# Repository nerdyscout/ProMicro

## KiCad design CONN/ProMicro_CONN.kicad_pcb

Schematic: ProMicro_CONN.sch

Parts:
A1: Sparkfun_Pro_Micro
C2: 1µ; C_0603_1608Metric; MPN CL10A105KB8NNNC; LCSC# C15849
C3: 100n; C_0603_1608Metric; MPN CC0603KRX7R9BB104; LCSC# C14663
D1: LED; LED_0603_1608Metric; MPN 19-217/GHC-YR1S2/3T; LCSC# C72043
J1: AVR-JTAG-10; IDC-Header_2x05_P2.54mm_Vertical
J2: UEXT_Host; UEXT
J3: Display; PinHeader_1x04_P2.54mm_Vertical
LOGO1: Logo_Open_Hardware_Small; OSHW-Symbol_6.7x6mm_SilkScreen
R1, R2, R3, R4, R5, R6, R7, R9: 4k7; R_0603_1608Metric; MPN 0603WAF4701T5E; LCSC# C23162
R8: 1k; R_0603_1608Metric
SW1: reset; SW_SPST_B3U-1000P; MPN B3U-1000P
SW2: user; SW_SPST_B3U-1000P; MPN B3U-1000P

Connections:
+3V3: A1.21, C3.1, J1.4 (VREF), J1.7 (VCC), J2.1 (3V3), J3.2, R1.2, R2.2, R3.2, R4.2, R5.2, R6.2, R7.2
BTN: A1.9, SW2.2
CIPO: A1.15, J2.7 (MISO)
COPI: A1.14, J2.8 (MOSI)
CS1: A1.12, J2.10 (~SSEL)
GND: A1.3, A1.4, A1.23, C2.2, C3.2, D1.1 (K), J1.2 (GND), J1.10 (GND), J2.2 (GND), J3.1, R9.1, SW1.1
unnamed: D1.2 (A), R8.1
unnamed: R9.2, SW2.1
RXD: A1.1, J2.4 (RXD)
SCK: A1.16, J2.9 (SCK)
SCL: A1.6, J2.5 (SCL), J3.3, R3.1
SDA: A1.5, J2.6 (SDA), J3.4, R4.1
TCK: A1.20, J1.1 (TCK), R6.1, R8.2
TDI: A1.17, J1.9 (TDI), R1.1
TDO: A1.18, J1.3 (TDO), R2.1
TMS: A1.19, J1.5 (TMS), R5.1
TXD: A1.2, J2.3 (TXD)
~RST: A1.22, C2.1, J1.6 (~SRST), R7.1, SW1.2

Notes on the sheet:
Attention: RXD & TXD are swapped here!
uses internal pull-up

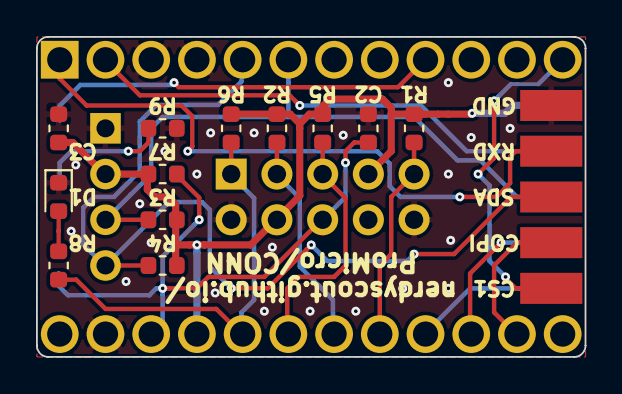
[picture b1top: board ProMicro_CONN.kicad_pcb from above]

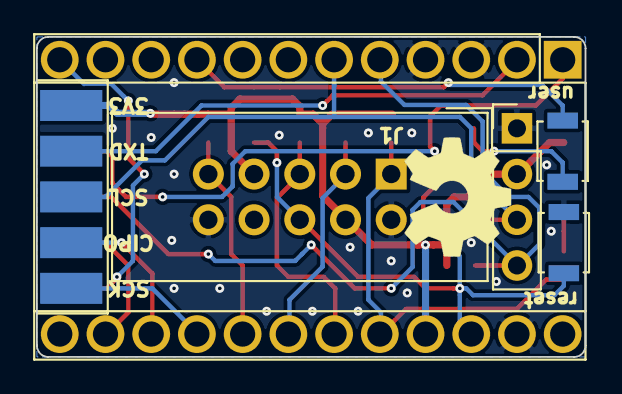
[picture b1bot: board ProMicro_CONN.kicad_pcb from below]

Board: 2 copper layers, 30.5 x 17.8 mm, 19 parts (7 on the bottom side), 18 nets.

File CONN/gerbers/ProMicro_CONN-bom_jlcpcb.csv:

Comment,Designator,Package,lcsc#,mpn
Sparkfun_Pro_Micro,A1,Sparkfun_Pro_Micro,,
100n,C3,C_0603_1608Metric,C14663,CC0603KRX7R9BB104
1µ,C2,C_0603_1608Metric,C15849,CL10A105KB8NNNC
LED,D1,LED_0603_1608Metric,C72043,19-217/GHC-YR1S2/3T
AVR-JTAG-10,J1,IDC-Header_2x05_P2.54mm_Vertical,,
Display,J3,PinHeader_1x04_P2.54mm_Vertical,,
UEXT_Host,J2,UEXT,,
Logo_Open_Hardware_Small,LOGO1,OSHW-Symbol_6.7x6mm_SilkScreen,,
1k,R8,R_0603_1608Metric,,
4k7,R1,R_0603_1608Metric,C23162,0603WAF4701T5E
4k7,R2,R_0603_1608Metric,C23162,0603WAF4701T5E
4k7,R3,R_0603_1608Metric,C23162,0603WAF4701T5E
4k7,R4,R_0603_1608Metric,C23162,0603WAF4701T5E
4k7,R5,R_0603_1608Metric,C23162,0603WAF4701T5E
4k7,R6,R_0603_1608Metric,C23162,0603WAF4701T5E
4k7,R7,R_0603_1608Metric,C23162,0603WAF4701T5E
4k7,R9,R_0603_1608Metric,C23162,0603WAF4701T5E
reset,SW1,SW_SPST_B3U-1000P,,B3U-1000P
user,SW2,SW_SPST_B3U-1000P,,B3U-1000P

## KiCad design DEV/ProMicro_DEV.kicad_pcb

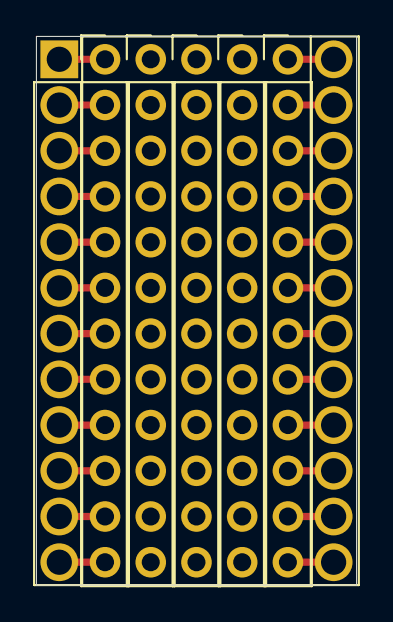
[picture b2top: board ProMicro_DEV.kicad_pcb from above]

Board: 2 copper layers, 17.8 x 30.5 mm, 6 parts (0 on the bottom side), 22 nets.

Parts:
A1: Sparkfun_Pro_Micro; ProMicro
J1, J2, J3, J4, J5: Conn_01x12; PinHeader_1x12_P2.54mm_Vertical

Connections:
+3V3: A1.21, J2.4
+5V: A1.24, J2.1
BTN: A1.9, J1.9
CIPO: A1.15, J2.10
COPI: A1.14, J2.11
CS0: A1.13, J2.12
CS1: A1.12, J1.12
D8: A1.11, J1.11
GND: A1.3, A1.4, A1.23, J1.3, J1.4, J2.2
INT: A1.10, J1.10
PWM: A1.8, J1.8
RXD: A1.1, J1.1
SCK: A1.16, J2.9
SCL: A1.6, J1.6
SDA: A1.5, J1.5
STAT: A1.7, J1.7
TCK: A1.20, J2.5
TDI: A1.17, J2.8
TDO: A1.18, J2.7
TMS: A1.19, J2.6
TXD: A1.2, J1.2
~RST: A1.22, J2.3

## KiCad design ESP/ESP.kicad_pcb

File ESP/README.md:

# ProMicro_ESP 
This module can be mounted to an [Arduino Pro Mini](https://www.sparkfun.com/products/11113), [Arduino Nano](https://store.arduino.cc/arduino-nano), [Sparkfun Pro Micro](https://www.sparkfun.com/products/12587), or any other pincompatible MCU running with 3.3V.

## Documentation 
All files can be found on [Github](https://github.com/nerdyscout/ProMicro/tree/master/ESP).

### Schematic

### BoM
  * [interactiveHTMLBoM](https://nerdyscout.github.io/ProMicro/ESP/docs/bom/ESP-ibom.html)
  * [octopart](docs/bom/ESP-bom_octopart.csv)

## Hardware 
### Layout

### Gerbers
can be found within the Github [repository](gerbers).

## Code  (unless otherwise stated)
 * [blink](examples/blink/blink.ino)

## external
### Links
  * [hackaday.io](https://hackaday.io/project/171898-promicro)

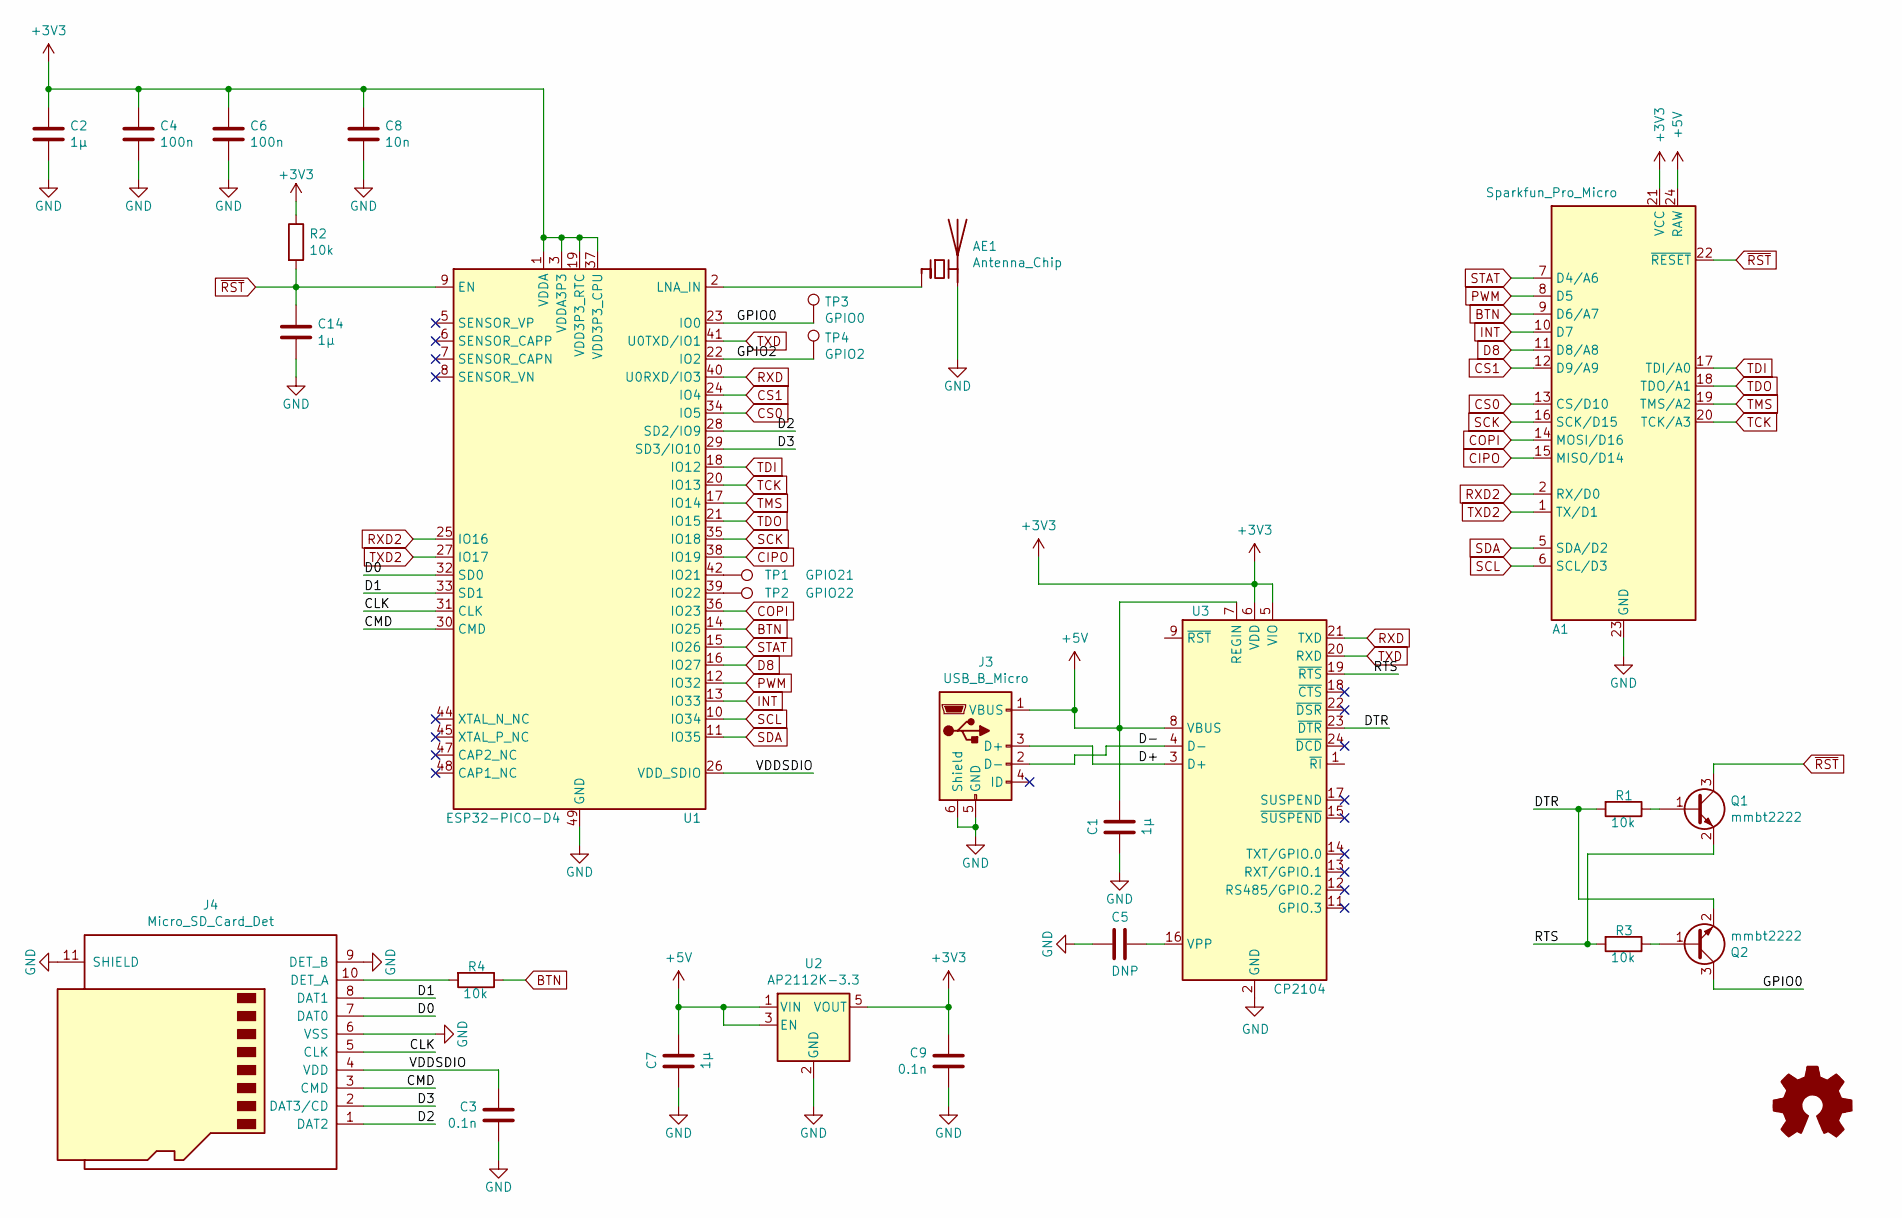
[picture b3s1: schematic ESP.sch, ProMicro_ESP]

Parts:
A1: Sparkfun_Pro_Micro; ProMicro
AE1: Antenna_Chip; SMD_ANT9520
C1, C2, C7, C14: 1µ; C_0603_1608Metric
C3, C9: 0.1n; C_0603_1608Metric
C4, C6: 100n; C_0603_1608Metric
C5: DNP; C_0603_1608Metric
C8: 10n; C_0603_1608Metric
J3: USB_B_Micro; USB_Micro-B_Molex_47346-0001
J4: Micro_SD_Card_Det; microSD_HC_Molex_104031-0811
LOGO1: Logo_Open_Hardware_Small; OSHW-Symbol_6.7x6mm_SilkScreen
Q1, Q2: mmbt2222; SOT-23
R1, R2, R3, R4: 10k; R_0603_1608Metric
TP1: GPIO21; PinHeader_1x01_P2.54mm_Vertical
TP2: GPIO22; PinHeader_1x01_P2.54mm_Vertical
TP3: GPIO0; PinHeader_1x01_P2.54mm_Vertical
TP4: GPIO2; PinHeader_1x01_P2.54mm_Vertical
U1: ESP32-PICO-D4; QFN-48-1EP_7x7mm_P0.5mm_EP5.3x5.3mm
U2: AP2112K-3.3; SOT-23-5
U3: CP2104; QFN-24-1EP_4x4mm_P0.5mm_EP2.6x2.6mm

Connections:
/CLK: J4.5 (CLK), U1.31 (CLK)
/CMD: J4.3 (CMD), U1.30 (CMD)
/D0: J4.7 (DAT0), U1.32 (SD0)
/D1: J4.8 (DAT1), U1.33 (SD1)
/D2: J4.1 (DAT2), U1.28 (SD2/IO9)
/D3: J4.2 (DAT3/CD), U1.29 (SD3/IO10)
/D+: J3.3 (D+), U3.3 (D+)
/D-: J3.2 (D-), U3.4 (D-)
/DTR: Q2.2 (E), R1.2, U3.23 (~DTR)
/GPIO0: Q2.3 (C), TP3.1, U1.23 (IO0)
/GPIO2: TP4.1, U1.22 (IO2)
/RTS: Q1.2 (E), R3.2, U3.19 (~RTS)
/VDDSDIO: C3.1, J4.4 (VDD), U1.26 (VDD_SDIO)
BTN: A1.9 (D6/A7), R4.1, U1.14 (IO25)
CIPO: A1.15 (MISO/D14), U1.38 (IO19)
COPI: A1.14 (MOSI/D16), U1.36 (IO23)
CS0: A1.13 (CS/D10), U1.34 (IO5)
CS1: A1.12 (D9/A9), U1.24 (IO4)
D8: A1.11 (D8/A8), U1.16 (IO27)
GND: A1.3 (GND), A1.4 (GND), A1.23 (GND), AE1.2 (PCB_Trace), C1.2, C2.2, C3.2, C4.2, C5.2, C6.2, C7.2, C8.2, C9.2, C14.2, J3.5 (GND), J3.6 (Shield), J4.6 (VSS), J4.9 (DET_B), J4.11 (SHIELD), U1.49 (GND), U2.2 (GND), U3.2 (GND), U3.25 (GND)
INT: A1.10 (D7), U1.13 (IO33)
unnamed: AE1.1 (FEED), U1.2 (LNA_IN)
unnamed: C5.1, U3.16 (VPP)
unnamed: J4.10 (DET_A), R4.2
unnamed: Q1.1 (B), R1.1
unnamed: Q2.1 (B), R3.1
unnamed: TP1.1, U1.42 (IO21)
unnamed: TP2.1, U1.39 (IO22)
PWM: A1.8 (D5), U1.12 (IO32)
RXD: U1.40 (U0RXD/IO3), U3.21 (TXD)
RXD2: A1.2 (RX/D0), U1.25 (IO16)
SCK: A1.16 (SCK/D15), U1.35 (IO18)
SCL: A1.6 (SCL/D3), U1.10 (IO34)
SDA: A1.5 (SDA/D2), U1.11 (IO35)
STAT: A1.7 (D4/A6), U1.15 (IO26)
TCK: A1.20 (TCK/A3), U1.20 (IO13)
TDI: A1.17 (TDI/A0), U1.18 (IO12)
TDO: A1.18 (TDO/A1), U1.21 (IO15)
TMS: A1.19 (TMS/A2), U1.17 (IO14)
TXD: U1.41 (U0TXD/IO1), U3.20 (RXD)
TXD2: A1.1 (TX/D1), U1.27 (IO17)
~RST: A1.22 (~RESET), C14.1, Q1.3 (C), R2.2, U1.9 (EN)

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
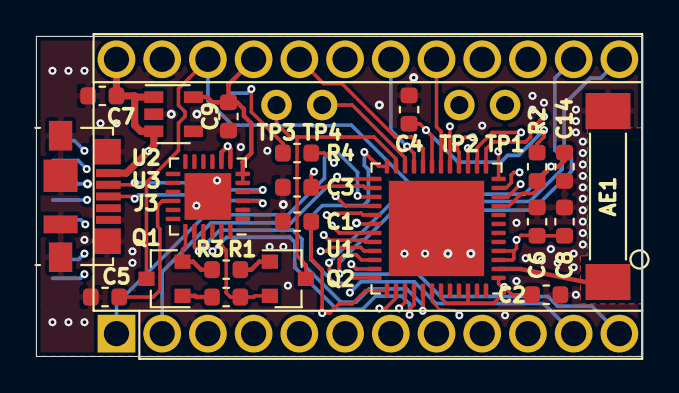
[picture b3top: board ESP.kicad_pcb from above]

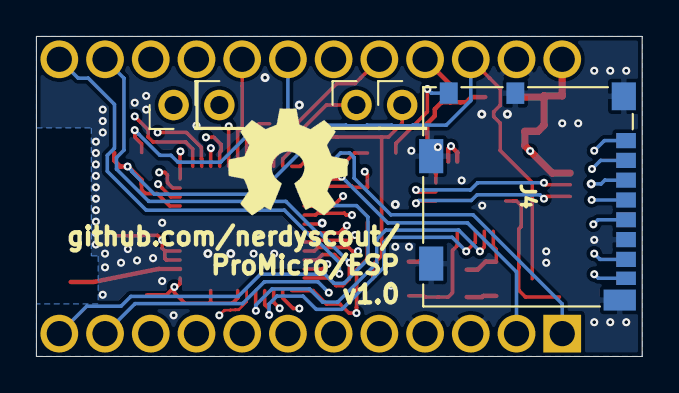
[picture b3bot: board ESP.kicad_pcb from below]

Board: 4 copper layers, 33.7 x 17.8 mm, 28 parts (6 on the bottom side), 44 nets.

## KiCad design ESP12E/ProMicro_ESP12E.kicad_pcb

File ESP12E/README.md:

# ProMicro_ESP12E
This module can be mounted to an [Arduino Pro Mini](https://www.sparkfun.com/products/11113), [Arduino Nano](https://store.arduino.cc/arduino-nano), [Sparkfun Pro Micro](https://www.sparkfun.com/products/12587), or any other pincompatible MCU running with 3.3V.

## Documentation
All files can be found on [Github](https://github.com/nerdyscout/ProMicro/tree/master/ESP12E).

### Schematic

### Layout

### BoM
  * [interactiveHTMLBoM](https://nerdyscout.github.io/ProMicro/ESP12E/docs/bom/ProMicro_ESP12E-ibom.html)
  * [octopart.csv](docs/bom/ProMicro_ESP12E-bom_octopart.csv)
  * [jlcpcb.csv](gerbers/ProMicro_ESP12E-bom_jlcpcb.csv)

## Gerbers
can be found within the Github [repository](gerbers).

## Links
  * [hackaday.io](https://hackaday.io/project/171898-promicro)

## License
Copyright Stefan Herold 2020

This documentation describes Open Hardware and is licensed under the CERN OHL v.1.2.

You may redistribute and modify this documentation under the terms of the CERN OHL v.1.2. (http://ohwr.org/cernohl). This documentation is distributed WITHOUT ANY EXPRESS OR IMPLIED WARRANTY, INCLUDING OF MERCHANTABILITY, SATISFACTORY QUALITY AND FITNESS FOR A PARTICULAR PURPOSE. Please see the CERN OHL v.1.2 for applicable conditions

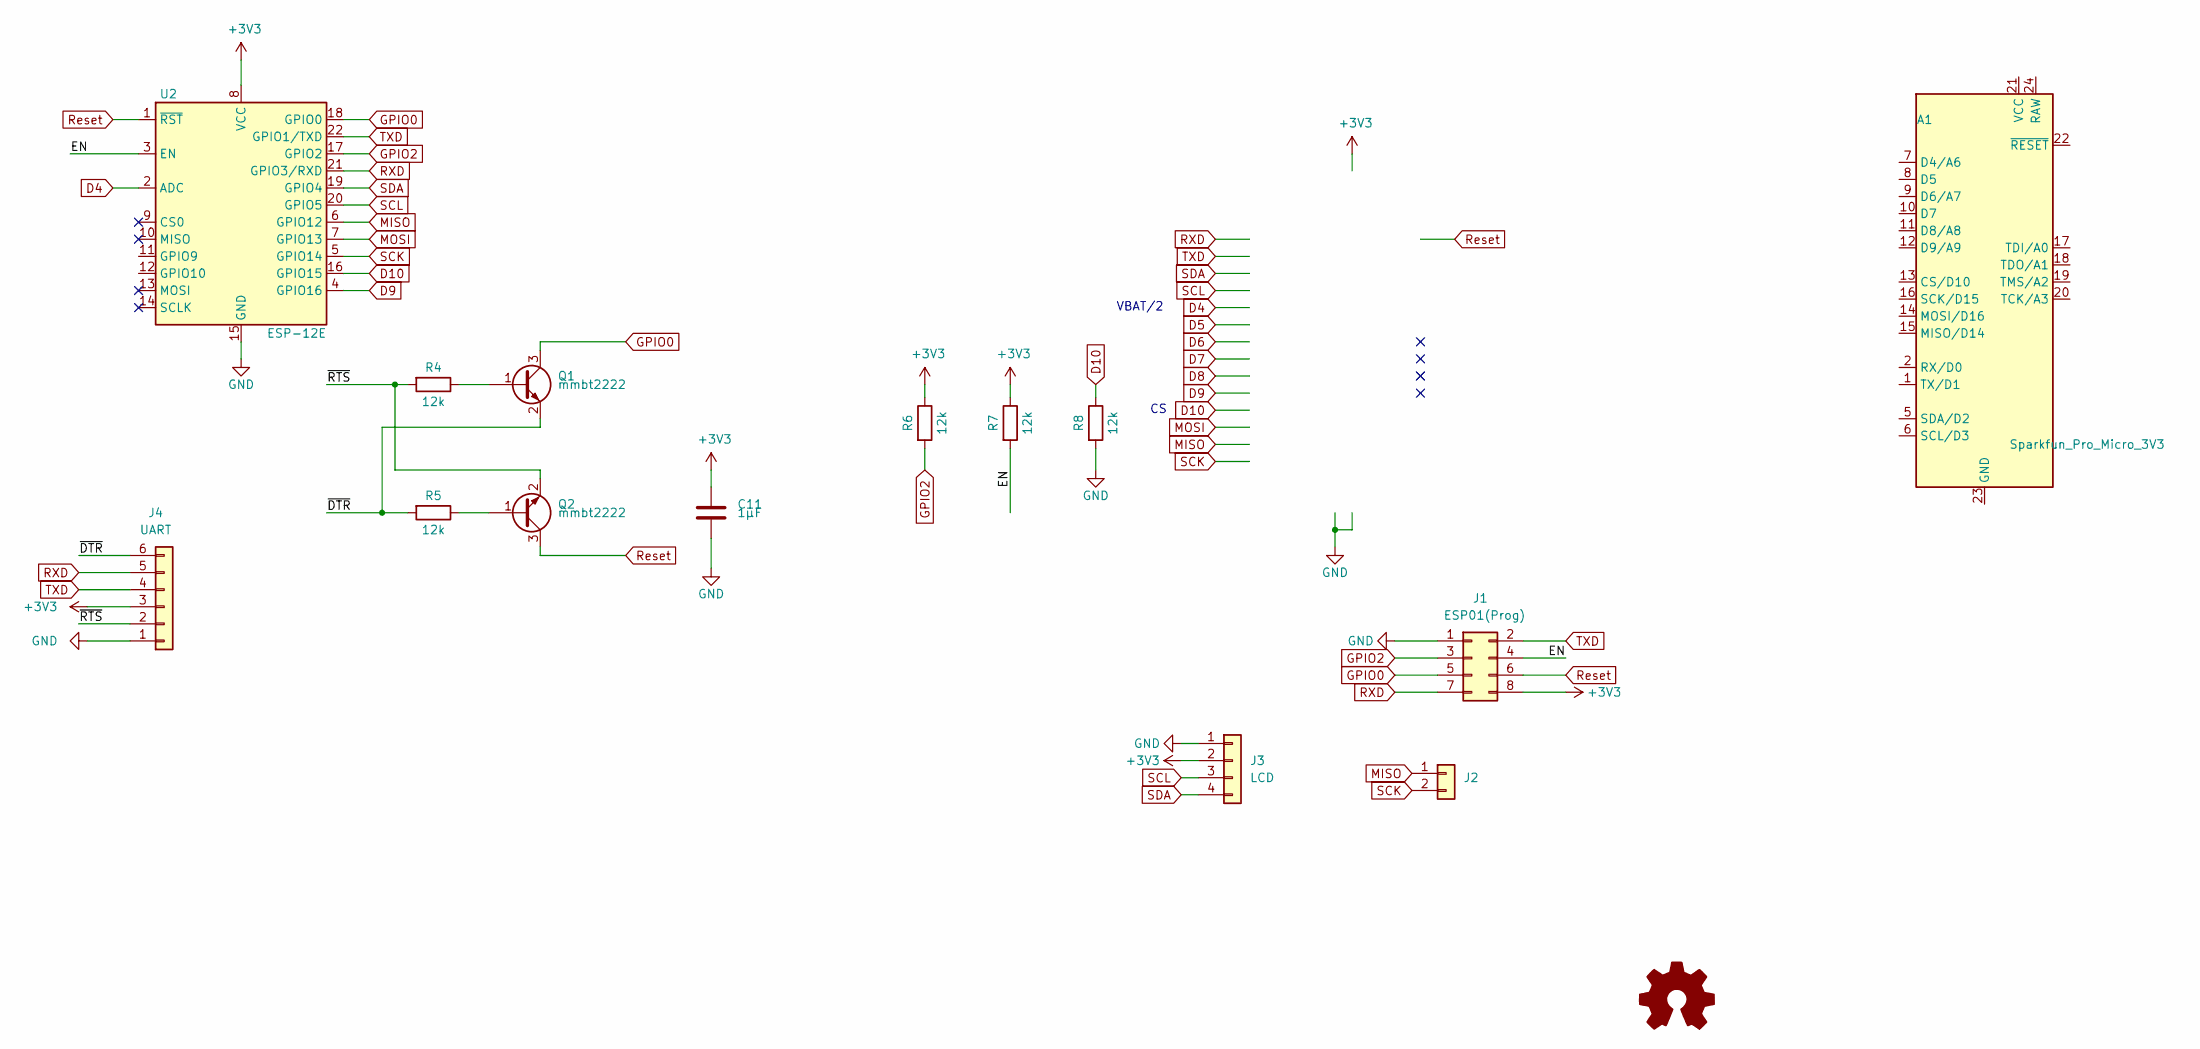
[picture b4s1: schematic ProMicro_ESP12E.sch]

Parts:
A1: Sparkfun_Pro_Micro_3V3; Sparkfun_Pro_Micro
C11: 1µF; C_0603_1608Metric
J1: ESP01(Prog); PinHeader_2x04_P2.54mm_Vertical
J2: Conn_01x02; PinHeader_1x02_P2.54mm_Vertical
J3: LCD; PinSocket_1x04_P2.54mm_Vertical
J4: UART; PinSocket_1x06_P2.54mm_Vertical
LOGO1: Logo_Open_Hardware_Small; OSHW-Symbol_6.7x6mm_SilkScreen
Q1, Q2: mmbt2222; SOT-23
R4, R5, R6, R7, R8: 12k; R_0603_1608Metric
U2: ESP-12E

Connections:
+3V3: A1.21 (VCC), C11.2, J1.8, J3.2, J4.3, R6.1, R7.1, U2.8 (VCC)
/EN: J1.4, R7.2, U2.3 (EN)
/~DTR: J4.6, Q1.2 (E), R5.2
/~RTS: J4.2, Q2.2 (E), R4.2
D4: A1.7 (D4/A6), U2.2 (ADC)
D9: A1.12 (D9/A9), U2.4 (GPIO16)
D10: A1.13 (CS/D10), R8.1, U2.16 (GPIO15)
GPIO0: J1.5, Q1.3 (C), U2.18 (GPIO0)
GPIO2: J1.3, R6.2, U2.17 (GPIO2)
MISO: A1.15 (MISO/D14), J2.1, U2.6 (GPIO12)
MOSI: A1.14 (MOSI/D16), U2.7 (GPIO13)
unnamed: Q1.1 (B), R4.1
unnamed: Q2.1 (B), R5.1
RXD: A1.2 (RX/D0), J1.7, J4.5, U2.21 (GPIO3/RXD)
Reset: A1.22 (~RESET), J1.6, Q2.3 (C), U2.1 (~RST)
SCK: A1.16 (SCK/D15), J2.2, U2.5 (GPIO14)
SCL: A1.6 (SCL/D3), J3.3, U2.20 (GPIO5)
SDA: A1.5 (SDA/D2), J3.4, U2.19 (GPIO4)
TXD: A1.1 (TX/D1), J1.2, J4.4, U2.22 (GPIO1/TXD)

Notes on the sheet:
VBAT/2

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
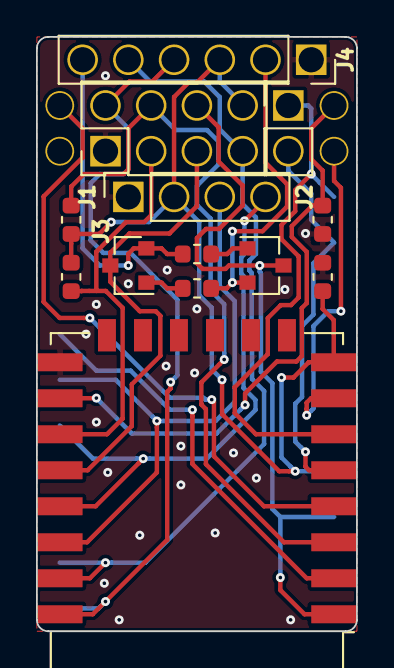
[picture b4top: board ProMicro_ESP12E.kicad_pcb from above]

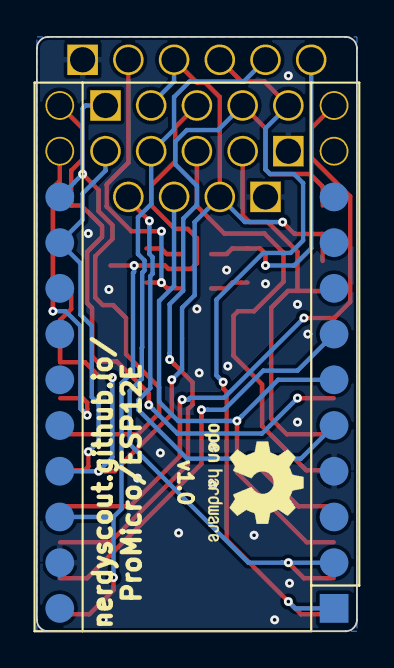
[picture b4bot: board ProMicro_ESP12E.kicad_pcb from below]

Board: 2 copper layers, 17.8 x 33.0 mm, 15 parts (2 on the bottom side), 20 nets.

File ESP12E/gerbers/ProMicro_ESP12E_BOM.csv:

Component;Description;Part;References;Value;Footprint;Quantity Per PCB;Datasheet
1;Unpolarized capacitor;C;C11;1µF;C_0603_1608Metric;1;~
2;Generic connector, single row, 01x02, script generated (kicad-library-utils/schlib/autogen/connector/);Conn_01x02;J2;Conn_01x02;PinHeader_1x02_P2.54mm_Vertical;1;~
3;Generic connector, double row, 02x04, odd/even pin numbering scheme (row 1 odd numbers, row 2 even numbers), script generated (kicad-library-utils/schlib/autogen/connector/);Conn_02x04_Odd_Even;J1;ESP01(Prog);PinHeader_2x04_P2.54mm_Vertical;1;~
4;Generic connector, single row, 01x04, script generated (kicad-library-utils/schlib/autogen/connector/);Conn_01x04;J3;LCD;PinSocket_1x04_P2.54mm_Vertical;1;~
5;Generic connector, single row, 01x06, script generated (kicad-library-utils/schlib/autogen/connector/);Conn_01x06;J4;UART;PinSocket_1x06_P2.54mm_Vertical;1;~
6;NPN transistor, base/emitter/collector;Q_NPN_BEC;Q1 Q2;mmbt2222;SOT-23;2;~
7;Resistor;R;R4 R5 R6 R7 R8;12k;R_0603_1608Metric;5;~
8;802.11 b/g/n Wi-Fi Module;ESP-12E;U2;ESP-12E;ESP-12E;1;http://wiki.ai-thinker.com/_media/esp8266/esp8266_series_mod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

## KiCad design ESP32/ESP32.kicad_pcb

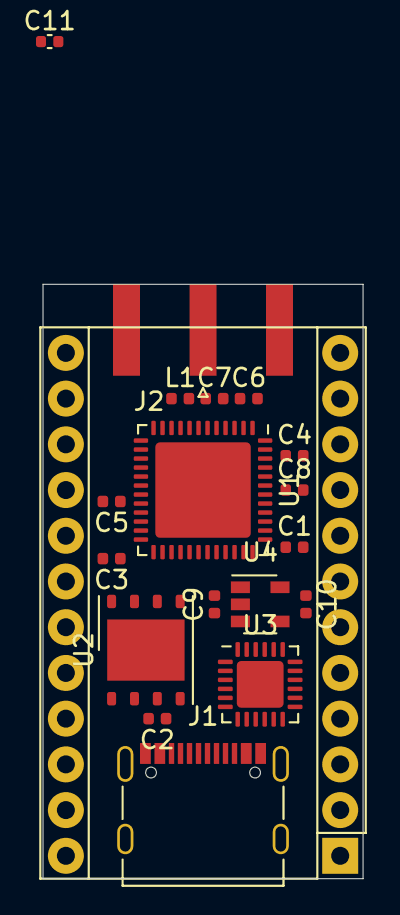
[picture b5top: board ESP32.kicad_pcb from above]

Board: 2 copper layers, 17.8 x 33.0 mm, 20 parts (1 on the bottom side), 24 nets, no tracks yet.

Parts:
A1: Sparkfun_Pro_Micro
C1, C2, C3, C4, C5, C8, C9, C10, C11: 100n; C_0402_1005Metric
C6: 0.75pF; C_0402_1005Metric
C7: 1.5pF; C_0402_1005Metric
J1: USB_C_Receptacle_USB2.0; USB_C_Receptacle_Palconn_UTC16-G
J2: Conn_Coaxial; SMA_Amphenol_132289_EdgeMount
L1: 7.5nH; L_0402_1005Metric
LOGO1: Logo_Open_Hardware_Small; OSHW-Symbol_6.7x6mm_SilkScreen
U1: ESP32-PICO-D4; QFN-48-1EP_7x7mm_P0.5mm_EP5.3x5.3mm
U2: W25Q32JVZP; WSON-8-1EP_6x5mm_P1.27mm_EP3.4x4.3mm
U3: CP2104; QFN-24-1EP_4x4mm_P0.5mm_EP2.6x2.6mm
U4: AP2112K-3.3; SOT-23-5

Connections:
+3V3: A1.21, C1.1, C4.1, C5.1, C8.1, C10.1, C11.1, U1.1, U1.3, U1.4, U1.19, U1.37, U1.43, U1.46, U4.5
/CMD: U1.30, U2.1
/D+: J1.A6, J1.B6, U3.3
/D-: J1.A7, J1.B7, U3.4
/DAT0: U1.32, U2.5
/DAT1: U1.33, U2.2
/DAT2: U1.28, U2.3
/DAT3: U1.29, U2.7
/SCLK: U1.31, U2.6
/VDD_SDIO: C3.1, U1.26, U2.8
GND: A1.3, A1.4, A1.23, C1.2, C2.2, C3.2, C4.2, C5.2, C6.2, C8.2, C9.2, C10.2, C11.2, J1.A1, J1.A12, J1.B1, J1.B12, J1.S1, J2.2, L1.1, U1.49, U2.4, U2.9, U3.2, U3.25, U4.2
unnamed: C6.1, C7.2, U1.2
unnamed: C7.1, J2.1, L1.2
unnamed: U3.5, U3.6
RXD: A1.1, U1.25
TCK: A1.20, U1.20
TDI: A1.17, U1.18
TDO: A1.18, U1.21
TMS: A1.19, U1.17
TXD: A1.2, U1.27
USB_RXD: U1.40, U3.21
USB_TXD: U1.41, U3.20
VBUS: C2.1, C9.1, J1.A4, J1.A9, J1.B4, J1.B9, U3.7, U3.8, U4.1, U4.3
~RST: A1.22, U1.9, U3.9

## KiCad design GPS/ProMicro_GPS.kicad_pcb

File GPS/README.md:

# ProMicro_GPS
This module can be mounted to an [Arduino Pro Mini](https://www.sparkfun.com/products/11113), [Arduino Nano](https://store.arduino.cc/arduino-nano), [Sparkfun Pro Micro](https://www.sparkfun.com/products/12587), or any other pincompatible MCU running with 3.3V. Depending on assembly it provides GPS and/or GYRO data. Manufacturing this PCB with 0.8mm thickness allows to mount a LORA module onto its back.

## Documentation
All files can be found on [Github](https://github.com/nerdyscout/ProMicro/tree/master/GPS).

### Schematic

### Layout

### BoM
  * [interactiveHTMLBoM](https://nerdyscout.github.io/ProMicro/GPS/docs/BOM/ProMicro_GPS.html)
  * [kicost](docs/BOM/ProMicro_GPS.xlsx)
  * [csv](docs/BOM/ProMicro_GPS.csv)

## Gerbers
can be found within the Github [repository](gerbers).

## Code
| | GYRO | GPS |
| --- | --- | --- |
| Arduino Nano | tbd | [GPS](examples/Arduino_Nano_GPS/Arduino_Nano_GPS.ino) |
| Sparkfun ProMicro | [ICM20948](examples/Sparkfun_ProMicro_ICM20948/Sparkfun_ProMicro_ICM20948.ino)<br>[MPU9250](examples/Sparkfun_ProMicro_MPU9250/Sparkfun_ProMicro_MPU9250.ino) | [GPS](examples/Sparkfun_ProMicro_GPS/Sparkfun_ProMicro_GPS.ino) |

## Links
  * [hackaday.io](https://hackaday.io/project/171898-promicro)

## License
Copyright Stefan Herold 2020

This documentation describes Open Hardware and is licensed under the CERN OHL v.1.2.

You may redistribute and modify this documentation under the terms of the CERN OHL v.1.2. (http://ohwr.org/cernohl). This documentation is distributed WITHOUT ANY EXPRESS OR IMPLIED WARRANTY, INCLUDING OF MERCHANTABILITY, SATISFACTORY QUALITY AND FITNESS FOR A PARTICULAR PURPOSE. Please see the CERN OHL v.1.2 for applicable conditions

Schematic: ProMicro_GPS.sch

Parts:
A1: Sparkfun_Pro_Micro_3V3; Sparkfun_Pro_Micro
C1: 100n; C_0402_1005Metric; LCSC# C15195
C2, C3, C4, C5, C7, C9: 100n; C_0402_1005Metric; LCSC# C1525
C6: 10n; C_0402_1005Metric; LCSC# C15195
C8: 4,7µ; C_0603_1608Metric; LCSC# C19666
C10, C11: DNP; C_0402_1005Metric
D1: LED; LED_0603_1608Metric; LCSC# C72041
H2: MountingHole; MountingHole_2.1mm
J1: uFL; U.FL_Hirose_U.FL-R-SMT-1_Vertical
J2: Coax; SMA_Samtec_SMA-J-P-H-ST-EM1_EdgeMount
JP1, JP4: SolderJumper_2_Open; SolderJumper-2_P1.3mm_Open_RoundedPad1.0x1.5mm
JP2: Jumper_NO_Small; SolderJumper-2_P1.3mm_Open_RoundedPad1.0x1.5mm
JP3: Jumper_NC_Small; SolderJumper-2_P1.3mm_Bridged_RoundedPad1.0x1.5mm
L1: 27n; L_0402_1005Metric
LOGO1: Logo_Open_Hardware_Small; OSHW-Symbol_6.7x6mm_SilkScreen
R1: 10; R_0402_1005Metric
R2: 0; R_0402_1005Metric; LCSC# C17168
R3: 1k; R_0402_1005Metric; LCSC# C11702
R4, R5: 4k7; R_0402_1005Metric; LCSC# C25900
TP1: AUX_SDA; TestPoint_Pad_D1.5mm
TP2: AUX_SCL; TestPoint_Pad_D1.5mm
TP3: FSYNC; TestPoint_Pad_D1.5mm
TP4: VBAT; TestPoint_THTPad_D1.5mm_Drill0.7mm
TP5, TP6: TestPoint; TestPoint_Pad_1.5x1.5mm
U1: MPU-9250; InvenSense_QFN-24_3x3mm_P0.4mm; LCSC# C71459
U2: AP2112K-1.8; SOT-23-5
U3: SIM28ML; ublox_MAX

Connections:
+1V8: C3.1, U1.8 (VDDIO), U2.5 (VOUT)
+3V3: A1.21, C1.1, C2.1, C4.1, C6.1, C7.1, C8.1, C9.1, R4.1, R5.1, U1.1 (RESV_VDDIO), U1.9 (AD0/MISO), U1.13 (VDD), U1.22 (~CS), U2.1 (VIN), U2.3 (EN), U3.7 (VCC_IO), U3.8 (VCC)
/INT: A1.10, JP1.2 (B)
/PWM: A1.8, JP4.1 (A)
/RXD: A1.1, JP2.2
/SCL: A1.6, R5.2, U1.23 (SCL/SCLK), U3.17 (SCL)
/SDA: A1.5, R4.2, U1.24 (SDA/MOSI), U3.16 (SDA)
/TXD: A1.2, JP3.2
/~RST: A1.22, U3.9 (~RESET)
GND: A1.4, A1.23, C1.2, C2.2, C3.2, C4.2, C5.2, C6.2, C7.2, C8.2, C9.2, C10.2, C11.2, D1.1 (K), J1.2, J2.2, TP5.1, TP6.1, U1.18 (GND), U1.20 (RESV_GND), U2.2 (GND), U3.1 (GND), U3.10 (GND), U3.12 (GND)
unnamed: C5.1, U1.10 (REGOUT)
unnamed: C10.1, R2.2, U3.11 (RF_IN)
unnamed: C11.1, J1.1, J2.1, L1.2, R2.1
unnamed: D1.2 (A), R3.1
unnamed: JP1.1 (A), U1.12 (INT)
unnamed: JP2.1, U3.3 (RXD)
unnamed: JP3.1, U3.2 (TXD)
unnamed: JP4.2 (B), U3.5 (EXTINT)
unnamed: L1.1, R1.1
unnamed: R1.2, U3.14 (VCC_RF)
unnamed: R3.2, U3.4 (TIMEPULSE)
unnamed: TP1.1, U1.21 (AUX_SDA)
unnamed: TP2.1, U1.7 (AUX_SCL)
unnamed: TP3.1, U1.11 (FSYNC)
unnamed: TP4.1, U3.6 (V_BCKP)

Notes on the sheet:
GYRO
GPS
active antenna only
Alternativ: MAX-8
TDI
TDO
TMS
TCK
SCK
CIPO
COPI
CS0
CS1
BTN
STAT

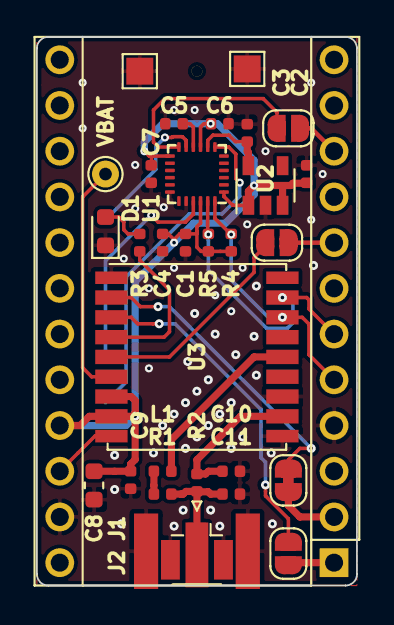
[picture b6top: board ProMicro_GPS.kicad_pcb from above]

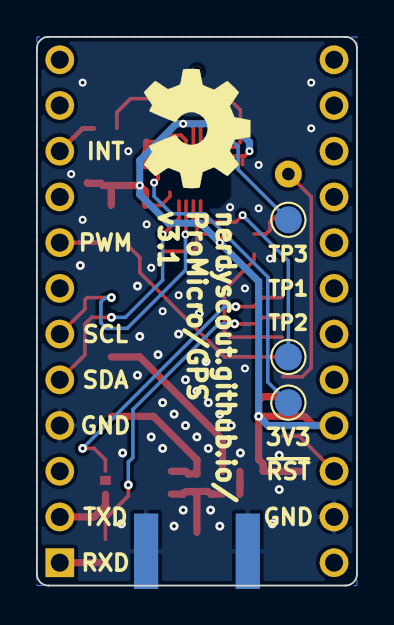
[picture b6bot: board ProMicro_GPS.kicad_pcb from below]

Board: 2 copper layers, 17.8 x 30.5 mm, 36 parts (4 on the bottom side), 25 nets.

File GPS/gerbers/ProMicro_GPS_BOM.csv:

Component;Description;Part;References;Value;Footprint;Quantity Per PCB;Datasheet;lcsc#;manf#;variant
1;Unpolarized capacitor;C;C6;10n;C_0402_1005Metric;1;~;C15195;CL05B103KB5NNNC;GYRO
2;Unpolarized capacitor;C;C1 C2 C3 C4 C5 C7 C9;100n;C_0402_1005Metric;7;~;C15195 C1525;CL05B103KB5NNNC CL05B104KO5NNNC;GYRO
3;Unpolarized capacitor;C;C8;4,7µ;C_0603_1608Metric;1;~;C19666;CL10A475KO8NNNC;
4;Light emitting diode;LED;D1;LED;LED_0603_1608Metric;1;~;C72041;19-217/BHC-ZL1M2RY/3T;GPS
5;Mounting Hole without connection;MountingHole;H2;MountingHole;MountingHole_2.1mm;1;~;;;
6;Generic connector, single row, 01x02, script generated (kicad-library-utils/schlib/autogen/connector/);Conn_01x02;J2;Coax;SMA_Samtec_SMA-J-P-H-ST-EM1_EdgeMount;1;~;;;DNP
7;Generic connector, single row, 01x02, script generated (kicad-library-utils/schlib/autogen/connector/);Conn_01x02;J1;uFL;U.FL_Hirose_U.FL-R-SMT-1_Vertical;1;~;;;DNP
8;Inductor;L;L1;27n;L_0402_1005Metric;1;~;;;DNP
9;Resistor;R;R2;0;R_0402_1005Metric;1;~;C17168;0402WGF0000TCE;GPS
10;Resistor;R;R1;10;R_0402_1005Metric;1;~;;;DNP
11;Resistor;R;R3;1k;R_0402_1005Metric;1;~;C11702;0402WGF1001TCE;GPS
12;Resistor;R;R4 R5;4k7;R_0402_1005Metric;2;~;C25900;0402WGF4701TCE;DNP
13;600mA low dropout linear regulator, with enable pin, 2.5V-6V input voltage range, 1.8V fixed positive output, SOT-23-5 package;AP2112K-1.8;U2;AP2112K-1.8;SOT-23-5;1;https://www.diodes.com/assets/Datasheets/AP2112.pdf;;;
14;InvenSense 9-Axis Motion Sensor, Accelerometer, Gyroscope, Compass, I2C/SPI;MPU-9250;U1;MPU-9250;InvenSense_QFN-24_3x3mm_P0.4mm;1;https://store.invensense.com/datasheets/invensense/MPU9250RE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;C71459;MPU-9250;GYRO
15;GNSS Module MAX M8, VCC 1.65V to 3.6V;MAX-8C;U3;SIM28ML;ublox_MAX;1;https://www.u-blox.com/sites/default/files/MAX-8_DataSheet_%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;;MAX-8C-0-10;GPS

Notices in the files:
ESP/README.md:
Documentation [![CC BY-SA](../img/ccbysa.png)](docs/LICENSE.TXT):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
